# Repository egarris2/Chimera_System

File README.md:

View this project on [CADLAB.io](https://cadlab.io/project/27528). 

# Chimera_System
A modular PCB system designed for rapid iteration and extreme flexibility in application.

All PCBs are designed in KiCAD 7. They utilize components that are available from the easyEDA component library which allows for quick generation of manufacturing files for order of assembly from JLCPCB.

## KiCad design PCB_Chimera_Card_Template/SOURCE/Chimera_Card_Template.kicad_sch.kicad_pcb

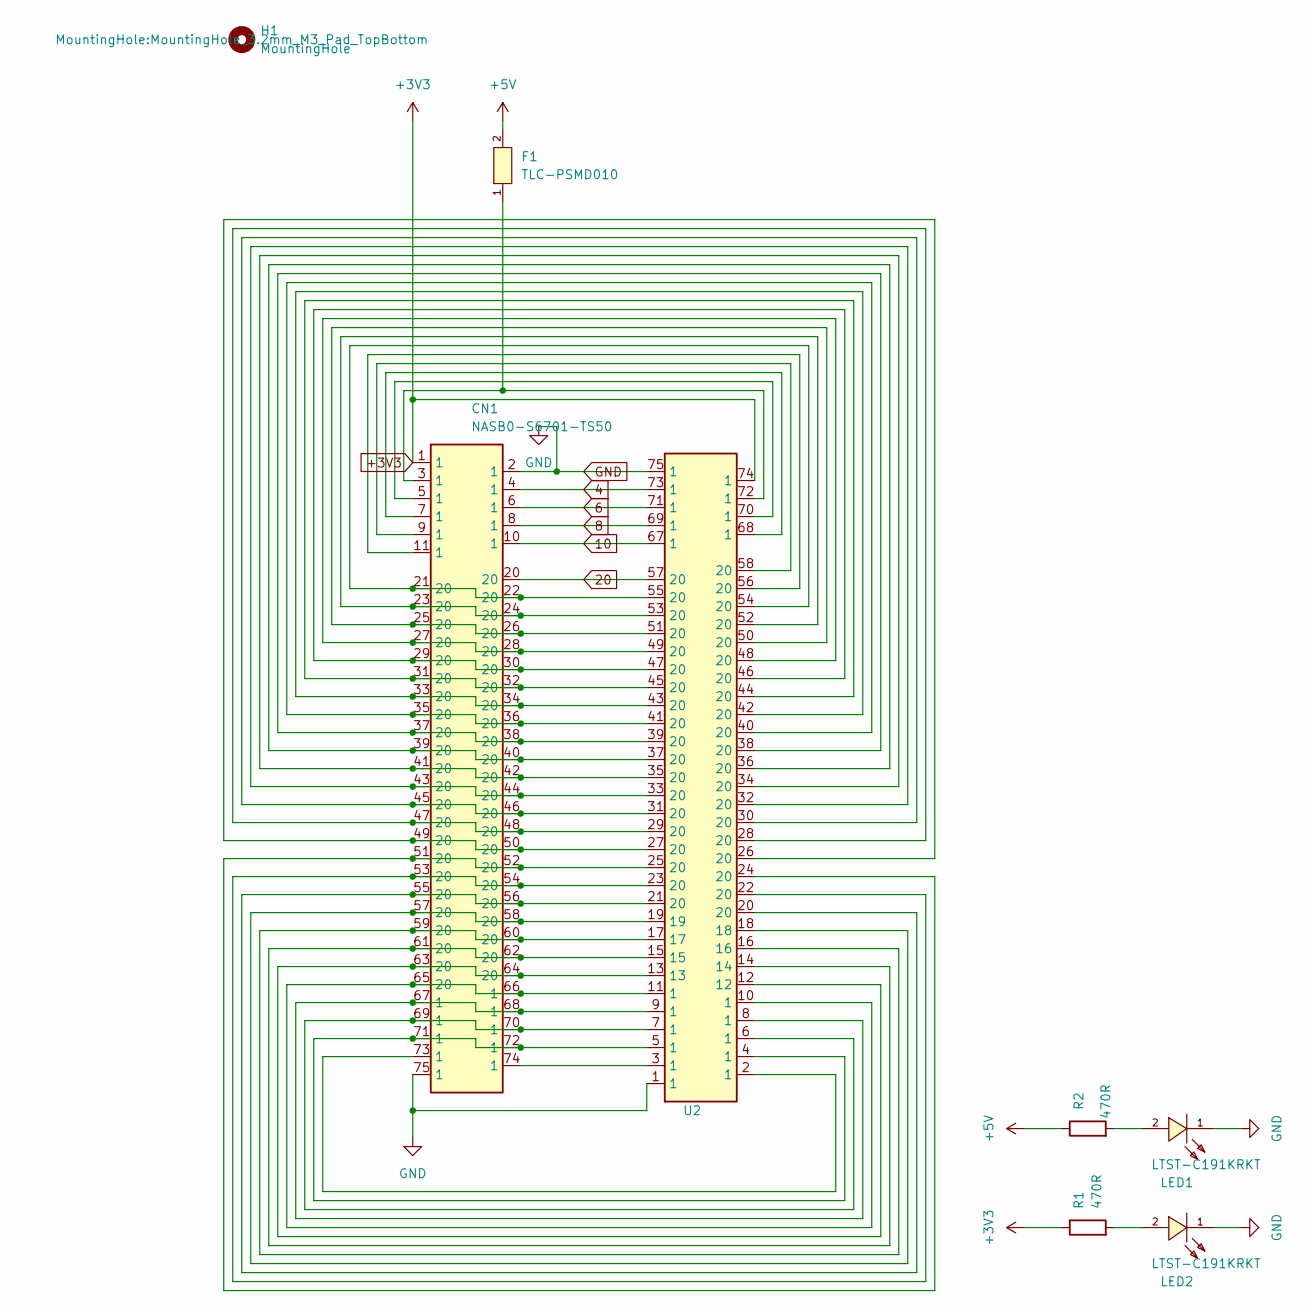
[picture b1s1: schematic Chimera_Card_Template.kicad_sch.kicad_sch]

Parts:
CN1: NASB0-S6701-TS50; CONN-SMD_67P-P0.50-V_NASB0-S6701-TS50; LCSC C367024
F1: TLC-PSMD010; F0805; LCSC C261939
H1: MountingHole; MountingHole_3.2mm_M3_Pad_TopBottom
LED1, LED2: LTST-C191KRKT; LED0603-RD; LCSC C125099
R1, R2: 470R; R_0603_1608Metric
U2: NGFF_M

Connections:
4: CN1.4 (1), U2.73 (1)
6: CN1.6 (1), U2.71 (1)
8: CN1.8 (1), U2.69 (1)
10: CN1.10 (1), U2.67 (1)
20: CN1.20, U2.57 (20)
+3V3: CN1.1, R1.1, U2.74 (1)
+5V: F1.2, R2.1
GND: CN1.2 (1), CN1.75 (1), LED1.1 (-), LED2.1 (-), U2.1, U2.75 (1)
unnamed: CN1.3 (1), F1.1, U2.72 (1)
unnamed: CN1.5 (1), U2.70 (1)
unnamed: CN1.7 (1), U2.68 (1)
unnamed: CN1.9 (1), U2.58 (20)
unnamed: CN1.11 (1), U2.56 (20)
unnamed: CN1.65 (20), CN1.66 (1), U2.10 (1), U2.11 (1)
unnamed: CN1.67 (1), CN1.68 (1), U2.8 (1), U2.9 (1)
unnamed: CN1.69 (1), CN1.70 (1), U2.6 (1), U2.7 (1)
unnamed: CN1.71 (1), CN1.72 (1), U2.4 (1), U2.5 (1)
unnamed: CN1.73 (1), U2.2 (1)
unnamed: CN1.74 (1), U2.3 (1)
unnamed: CN1.21 (20), CN1.22 (20), U2.54 (20), U2.55 (20)
unnamed: CN1.23 (20), CN1.24 (20), U2.52 (20), U2.53 (20)
unnamed: CN1.25 (20), CN1.26 (20), U2.50 (20), U2.51 (20)
unnamed: CN1.27 (20), CN1.28 (20), U2.48 (20), U2.49 (20)
unnamed: CN1.29 (20), CN1.30 (20), U2.46 (20), U2.47 (20)
unnamed: CN1.31 (20), CN1.32 (20), U2.44 (20), U2.45 (20)
unnamed: CN1.33 (20), CN1.34 (20), U2.42 (20), U2.43 (20)
unnamed: CN1.35 (20), CN1.36 (20), U2.40 (20), U2.41 (20)
unnamed: CN1.37 (20), CN1.38 (20), U2.38 (20), U2.39 (20)
unnamed: CN1.39 (20), CN1.40 (20), U2.36 (20), U2.37 (20)
unnamed: CN1.41 (20), CN1.42 (20), U2.34 (20), U2.35 (20)
unnamed: CN1.43 (20), CN1.44 (20), U2.32 (20), U2.33 (20)
unnamed: CN1.45 (20), CN1.46 (20), U2.30 (20), U2.31 (20)
unnamed: CN1.47 (20), CN1.48 (20), U2.28 (20), U2.29 (20)
unnamed: CN1.49 (20), CN1.50 (20), U2.26 (20), U2.27 (20)
unnamed: CN1.51 (20), CN1.52 (20), U2.24 (20), U2.25 (20)
unnamed: CN1.53 (20), CN1.54 (20), U2.22 (20), U2.23 (20)
unnamed: CN1.55 (20), CN1.56 (20), U2.20, U2.21 (20)
unnamed: CN1.57 (20), CN1.58 (20), U2.18, U2.19
unnamed: CN1.59 (20), CN1.60 (20), U2.16, U2.17
unnamed: CN1.61 (20), CN1.62 (20), U2.14, U2.15
unnamed: CN1.63 (20), CN1.64 (20), U2.12, U2.13
unnamed: LED1.2 (+), R2.2
unnamed: LED2.2 (+), R1.2

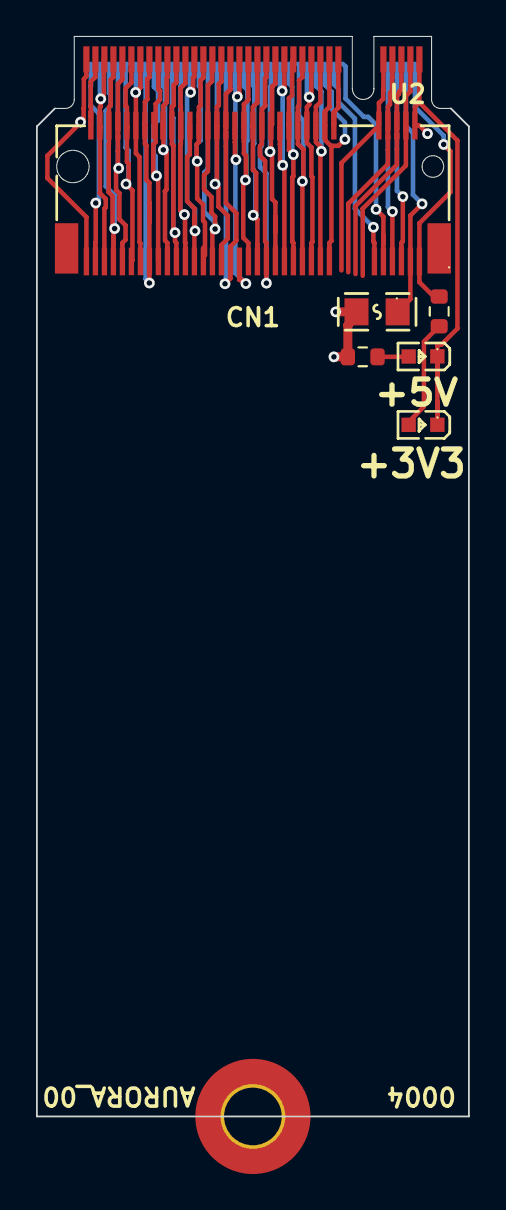
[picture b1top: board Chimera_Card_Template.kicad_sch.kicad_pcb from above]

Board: 4 copper layers, 24.0 x 60.0 mm, 8 parts (0 on the bottom side), 43 nets.

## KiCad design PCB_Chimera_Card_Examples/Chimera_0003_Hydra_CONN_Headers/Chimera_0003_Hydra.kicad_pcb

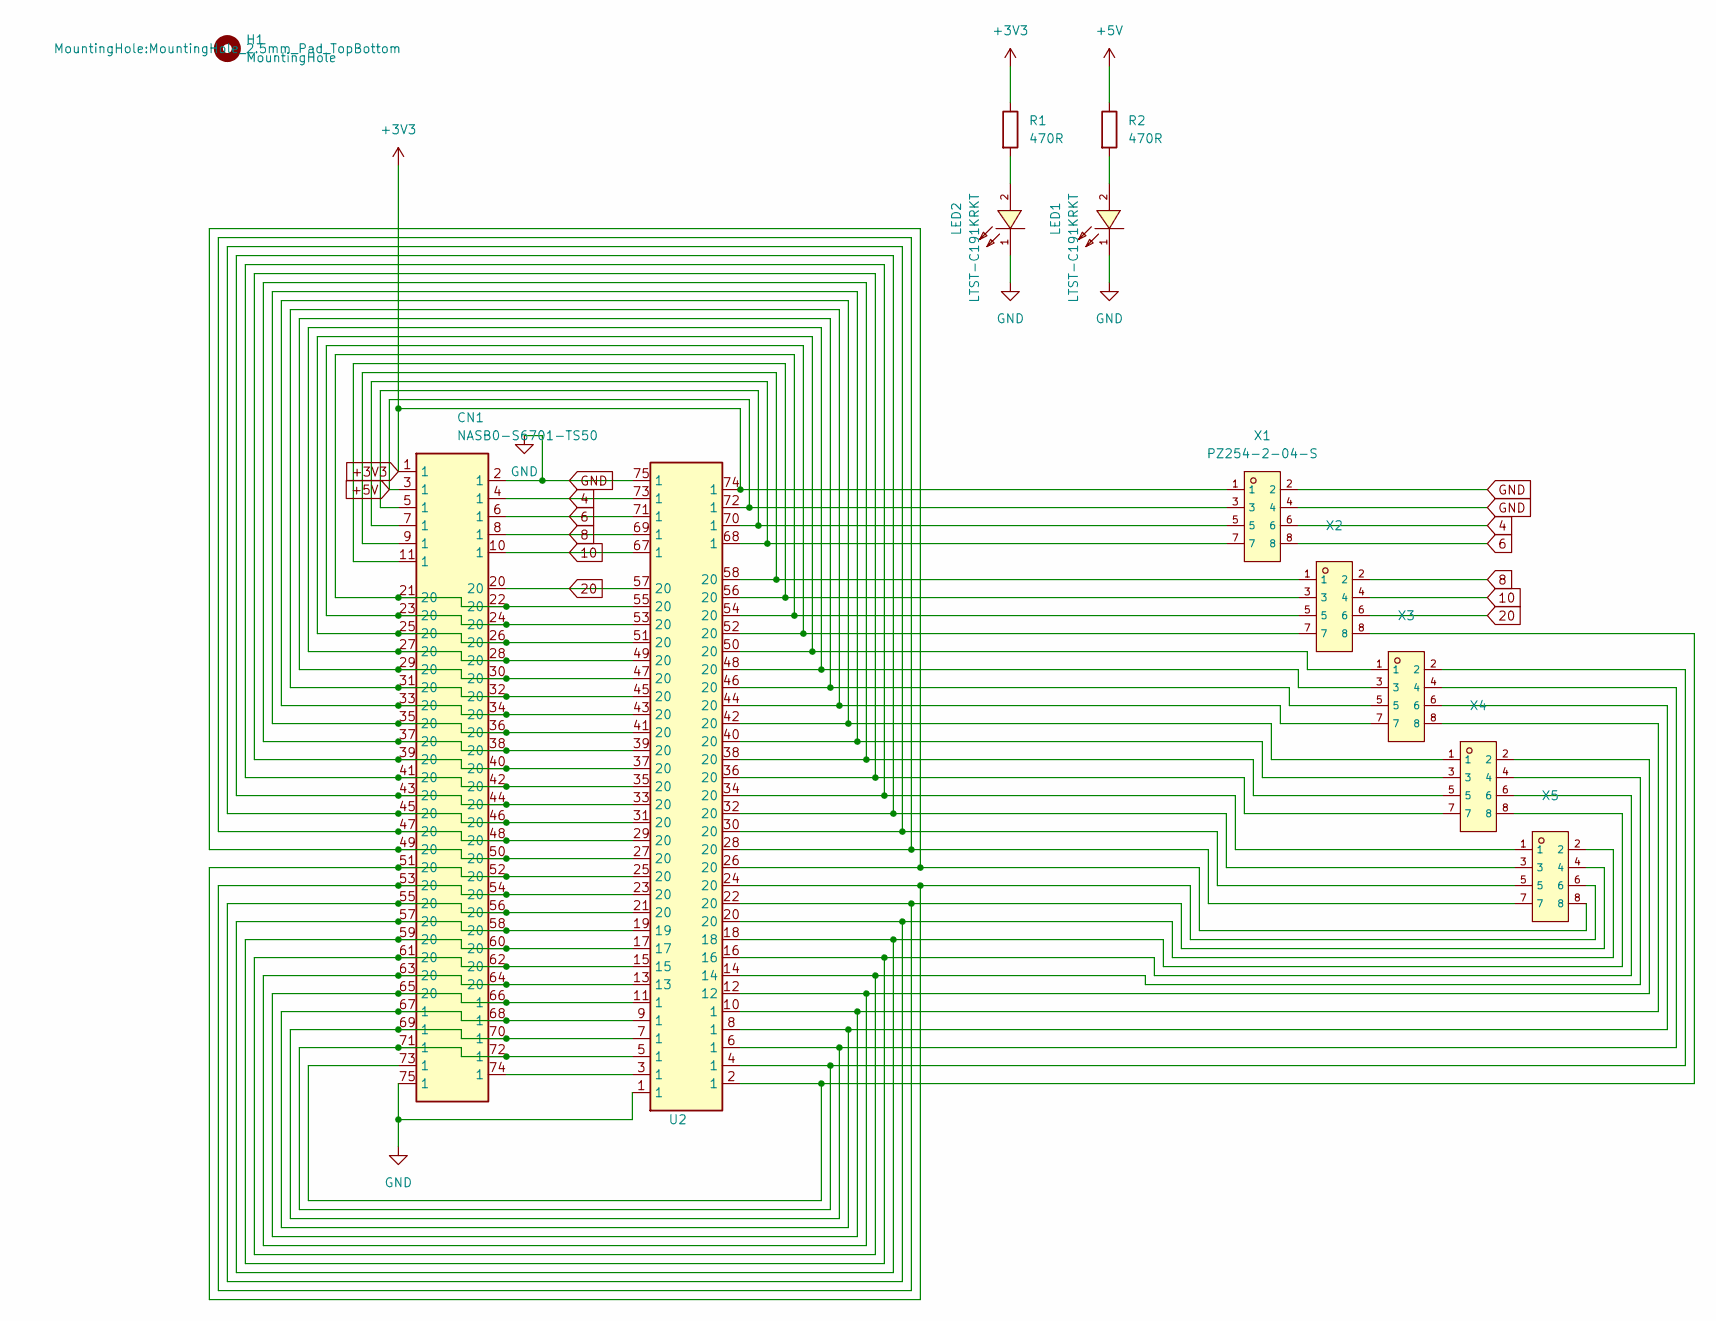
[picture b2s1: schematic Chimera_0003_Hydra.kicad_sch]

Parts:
CN1: NASB0-S6701-TS50; CONN-SMD_67P-P0.50-V_NASB0-S6701-TS50; LCSC C367024
H1: MountingHole; MountingHole_2.5mm_Pad_TopBottom
LED1, LED2: LTST-C191KRKT; LED0603-RD; LCSC C125099
R1, R2: 470R; R_0603_1608Metric
U2: NGFF_M
X1, X2, X3, X4, X5: PZ254-2-04-S; HDR-SMD_8P-P2.54-V-M-R2-C4-LS7.4; LCSC C3294462

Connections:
4: CN1.4 (1), U2.73 (1), X1.6
6: CN1.6 (1), U2.71 (1), X1.8
8: CN1.8 (1), U2.69 (1), X2.2
10: CN1.10 (1), U2.67 (1), X2.4
20: CN1.20, U2.57 (20), X2.6
+3V3: CN1.1, R1.1, U2.74 (1), X1.1
+5V: CN1.3 (1), R2.1, U2.72 (1), X1.3
GND: CN1.2 (1), CN1.75 (1), LED1.1 (-), LED2.1 (-), U2.1, U2.75 (1), X1.2, X1.4
unnamed: CN1.5 (1), U2.70 (1), X1.5
unnamed: CN1.7 (1), U2.68 (1), X1.7
unnamed: CN1.9 (1), U2.58 (20), X2.1
unnamed: CN1.11 (1), U2.56 (20), X2.3
unnamed: CN1.65 (20), CN1.66 (1), U2.10 (1), U2.11 (1), X3.8
unnamed: CN1.67 (1), CN1.68 (1), U2.8 (1), U2.9 (1), X3.6
unnamed: CN1.69 (1), CN1.70 (1), U2.6 (1), U2.7 (1), X3.4
unnamed: CN1.71 (1), CN1.72 (1), U2.4 (1), U2.5 (1), X3.2
unnamed: CN1.73 (1), U2.2 (1), X2.8
unnamed: CN1.74 (1), U2.3 (1)
unnamed: CN1.21 (20), CN1.22 (20), U2.54 (20), U2.55 (20), X2.5
unnamed: CN1.23 (20), CN1.24 (20), U2.52 (20), U2.53 (20), X2.7
unnamed: CN1.25 (20), CN1.26 (20), U2.50 (20), U2.51 (20), X3.1
unnamed: CN1.27 (20), CN1.28 (20), U2.48 (20), U2.49 (20), X3.3
unnamed: CN1.29 (20), CN1.30 (20), U2.46 (20), U2.47 (20), X3.5
unnamed: CN1.31 (20), CN1.32 (20), U2.44 (20), U2.45 (20), X3.7
unnamed: CN1.33 (20), CN1.34 (20), U2.42 (20), U2.43 (20), X4.1
unnamed: CN1.35 (20), CN1.36 (20), U2.40 (20), U2.41 (20), X4.3
unnamed: CN1.37 (20), CN1.38 (20), U2.38 (20), U2.39 (20), X4.5
unnamed: CN1.39 (20), CN1.40 (20), U2.36 (20), U2.37 (20), X4.7
unnamed: CN1.41 (20), CN1.42 (20), U2.34 (20), U2.35 (20), X5.1
unnamed: CN1.43 (20), CN1.44 (20), U2.32 (20), U2.33 (20), X5.3
unnamed: CN1.45 (20), CN1.46 (20), U2.30 (20), U2.31 (20), X5.5
unnamed: CN1.47 (20), CN1.48 (20), U2.28 (20), U2.29 (20), X5.7
unnamed: CN1.49 (20), CN1.50 (20), U2.26 (20), U2.27 (20), X5.8
unnamed: CN1.51 (20), CN1.52 (20), U2.24 (20), U2.25 (20), X5.6
unnamed: CN1.53 (20), CN1.54 (20), U2.22 (20), U2.23 (20), X5.4
unnamed: CN1.55 (20), CN1.56 (20), U2.20, U2.21 (20), X5.2
unnamed: CN1.57 (20), CN1.58 (20), U2.18, U2.19, X4.8
unnamed: CN1.59 (20), CN1.60 (20), U2.16, U2.17, X4.6
unnamed: CN1.61 (20), CN1.62 (20), U2.14, U2.15, X4.4
unnamed: CN1.63 (20), CN1.64 (20), U2.12, U2.13, X4.2
unnamed: LED1.2 (+), R2.2
unnamed: LED2.2 (+), R1.2

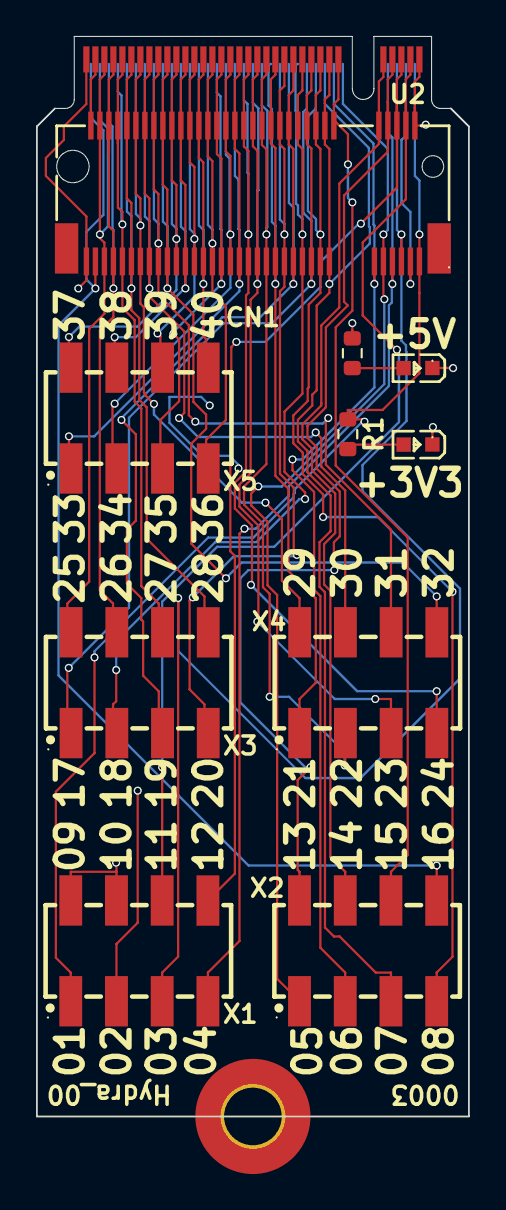
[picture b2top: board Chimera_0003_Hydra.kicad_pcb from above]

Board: 4 copper layers, 24.0 x 60.0 mm, 12 parts (0 on the bottom side), 42 nets.

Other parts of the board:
H2: MountingHole; MountingHole_3.2mm_M3_Pad_TopBottom

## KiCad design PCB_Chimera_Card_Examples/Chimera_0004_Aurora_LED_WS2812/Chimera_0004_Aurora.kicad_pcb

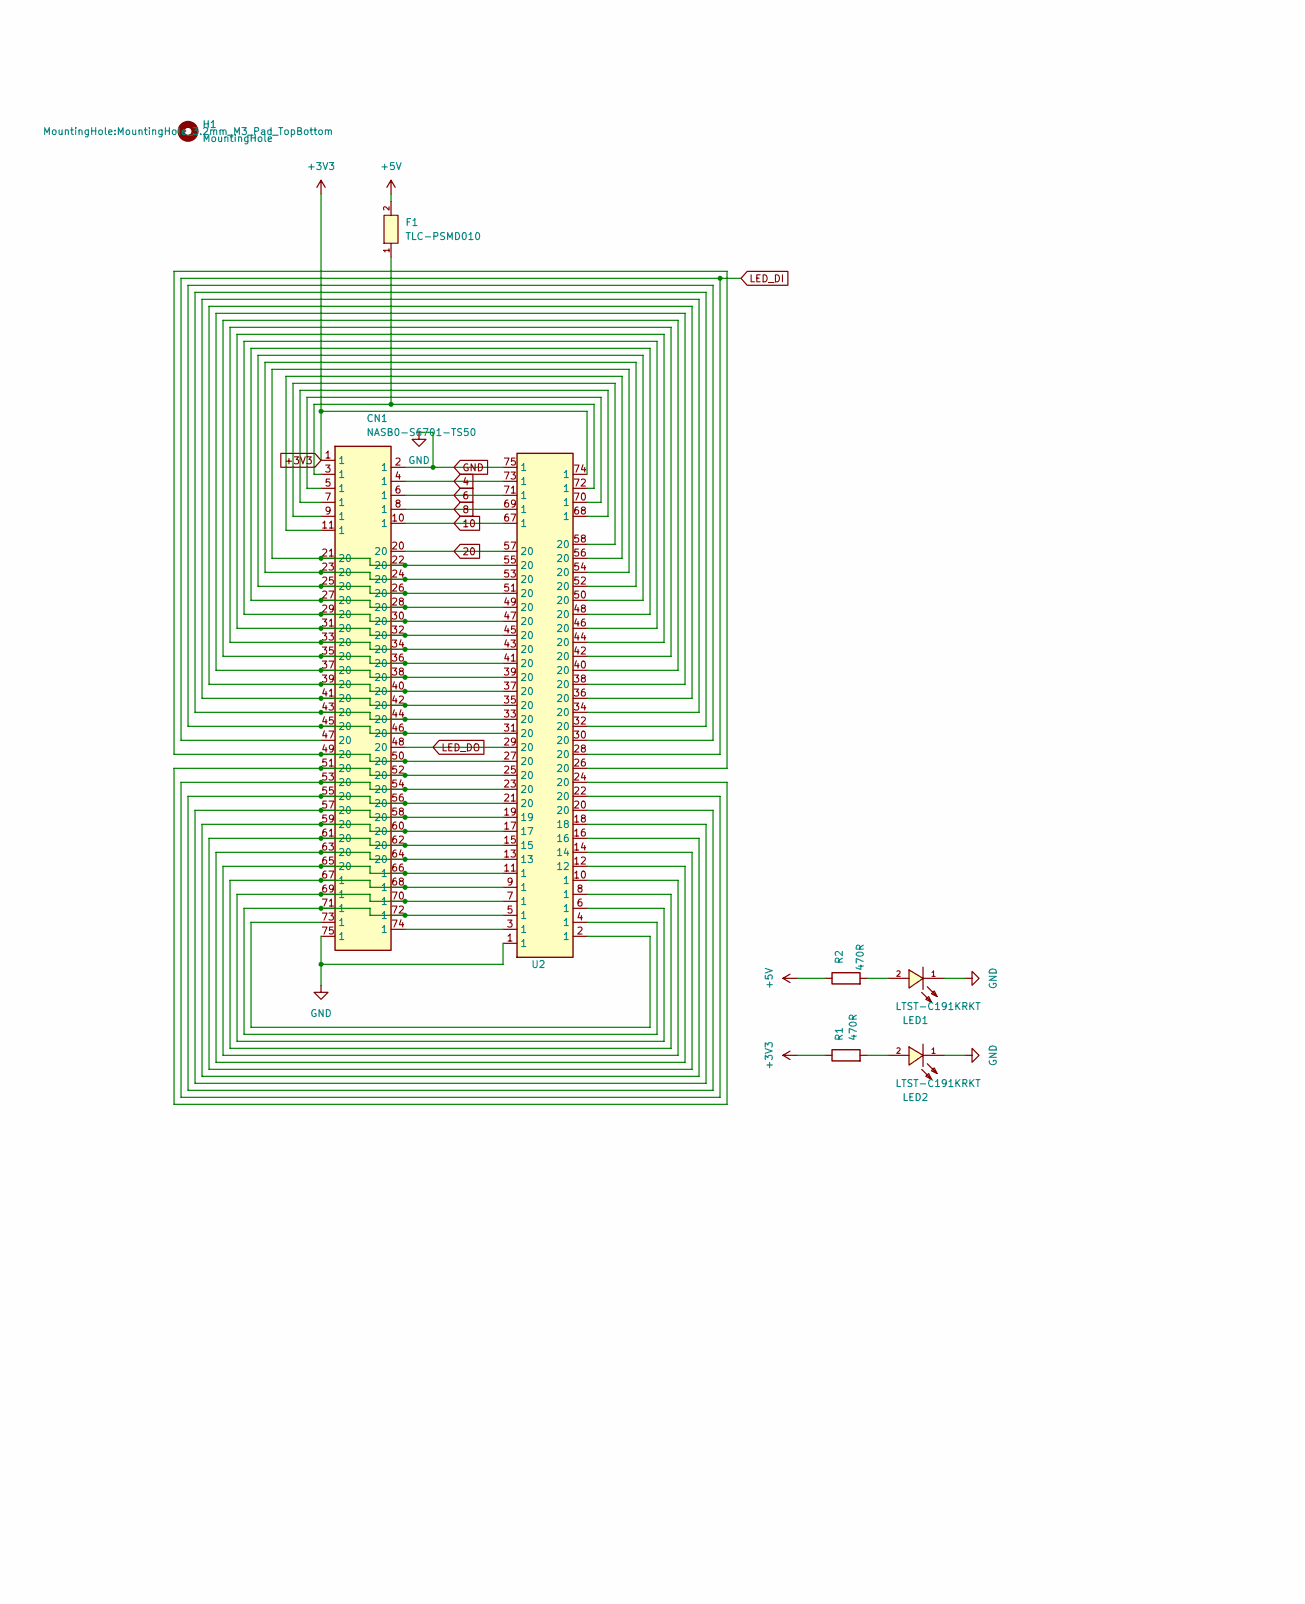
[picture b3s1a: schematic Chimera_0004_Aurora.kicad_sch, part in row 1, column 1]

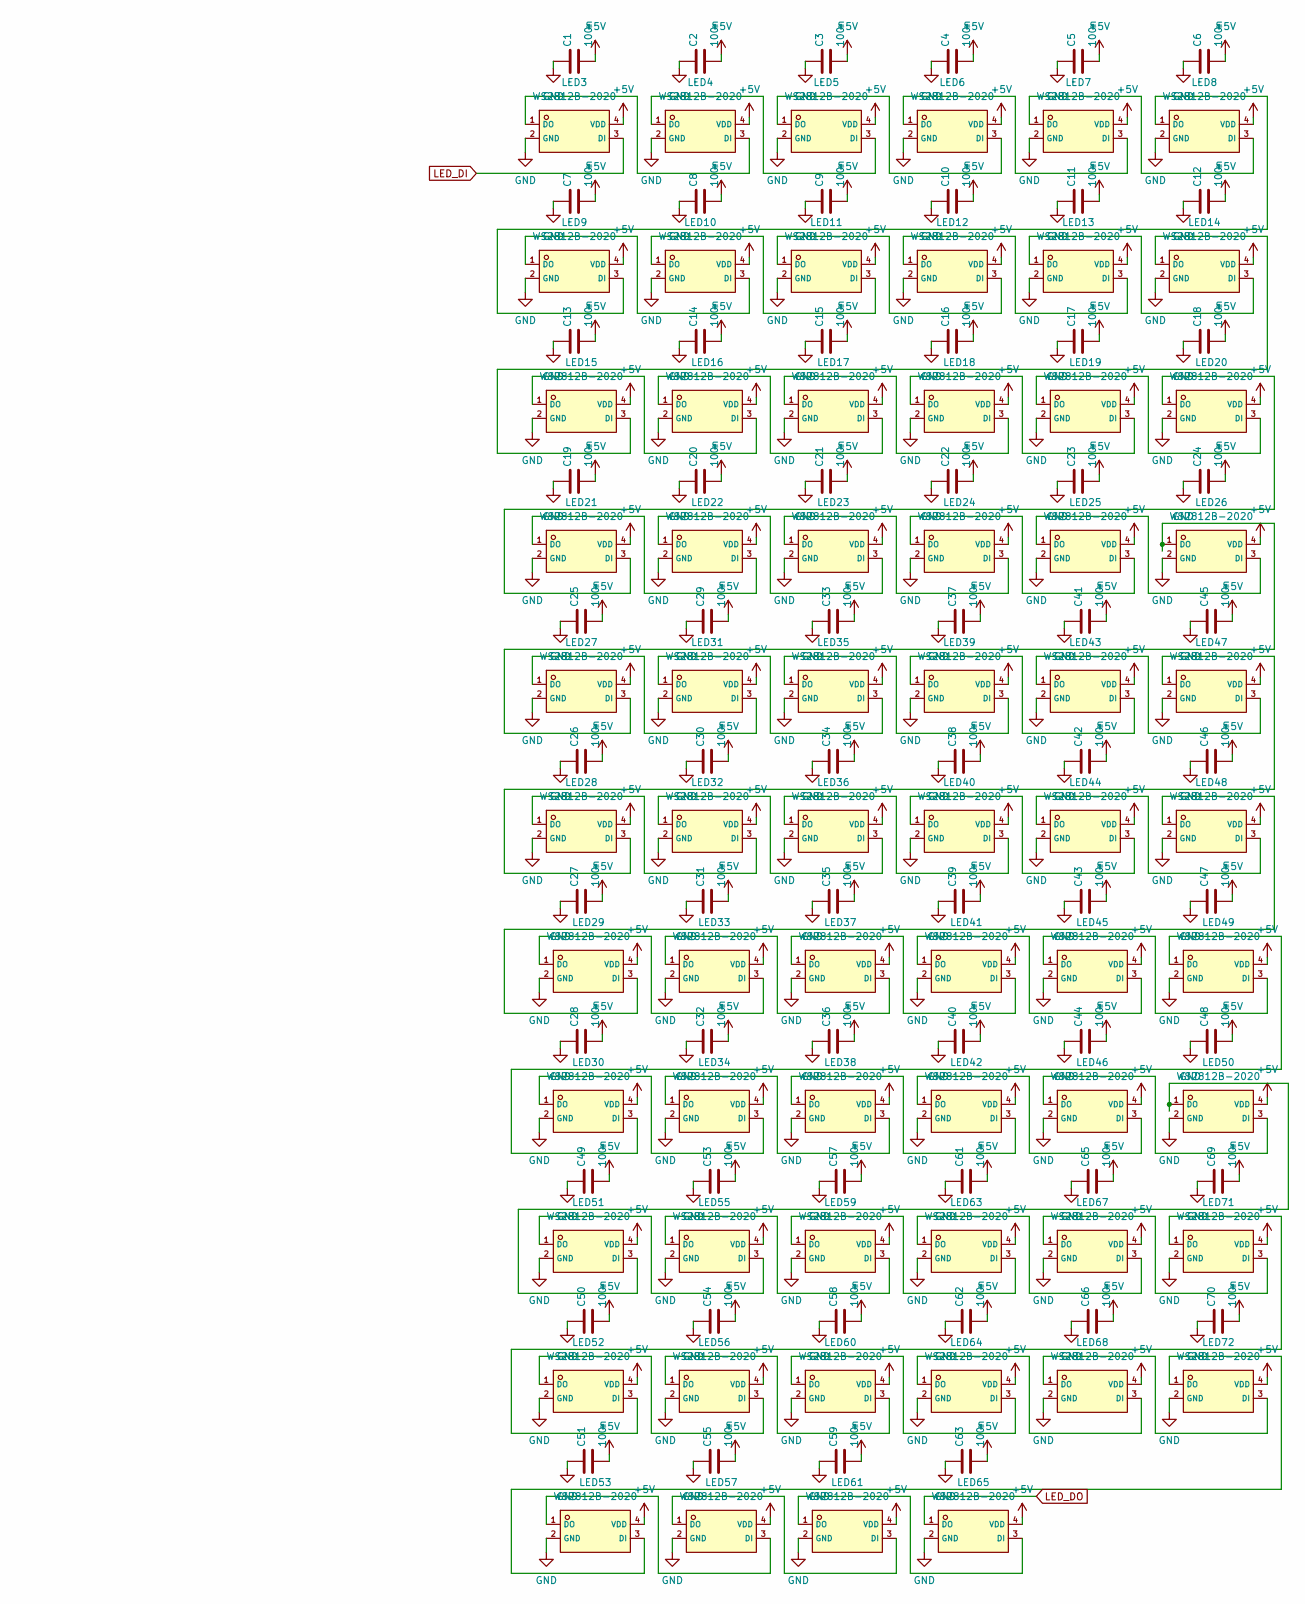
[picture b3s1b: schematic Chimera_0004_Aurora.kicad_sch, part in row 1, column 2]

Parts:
C1, C2, C3, C4, C5, C6, C7, C8, C9, C10, C11, C12, C13, C14, C15, C16, C17, C18, C19, C20, C21, C22, C23, C24, C25, C26, C27, C28, C29, C30, C31, C32, C33, C34, C35, C36, C37, C38, C39, C40, C41, C42, C43, C44, C45, C46, C47, C48, C49, C50, C51, C53, C54, C55, C57, C58, C59, C61, C62, C63, C65, C66, C69, C70: 100n; C_0402_1005Metric
CN1: NASB0-S6701-TS50; CONN-SMD_67P-P0.50-V_NASB0-S6701-TS50; LCSC C367024
F1: TLC-PSMD010; F0805; LCSC C261939
H1: MountingHole; MountingHole_3.2mm_M3_Pad_TopBottom
LED1, LED2: LTST-C191KRKT; LED0603-RD; LCSC C125099
LED3, LED4, LED5, LED6, LED7, LED8, LED9, LED10, LED11, LED12, LED13, LED14, LED15, LED16, LED17, LED18, LED19, LED20, LED21, LED22, LED23, LED24, LED25, LED26, LED27, LED28, LED29, LED30, LED31, LED32, LED33, LED34, LED35, LED36, LED37, LED38, LED39, LED40, LED41, LED42, LED43, LED44, LED45, LED46, LED47, LED48, LED49, LED50, LED51, LED52, LED53, LED55, LED56, LED57, LED59, LED60, LED61, LED63, LED64, LED65, LED67, LED68, LED71, LED72: WS2812B-2020; LED-SMD_4P-L2.0-W2.0-TL_WS2812B-2020; LCSC C965555
R1, R2: 470R; R_0603_1608Metric
U2: NGFF_M

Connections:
4: CN1.4 (1), U2.73 (1)
6: CN1.6 (1), U2.71 (1)
8: CN1.8 (1), U2.69 (1)
10: CN1.10 (1), U2.67 (1)
20: CN1.20, U2.57 (20)
+3V3: CN1.1, R1.1, U2.74 (1)
+5V: C1.2, C2.2, C3.2, C4.2, C5.2, C6.2, C7.2, C8.2, C9.2, C10.2, C11.2, C12.2, C13.2, C14.2, C15.2, C16.2, C17.2, C18.2, C19.2, C20.2, C21.2, C22.2, C23.2, C24.2, C25.2, C26.2, C27.2, C28.2, C29.2, C30.2, C31.2, C32.2, C33.2, C34.2, C35.2, C36.2, C37.2, C38.2, C39.2, C40.2, C41.2, C42.2, C43.2, C44.2, C45.2, C46.2, C47.2, C48.2, C49.2, C50.2, C51.2, C53.2, C54.2, C55.2, C57.2, C58.2, C59.2, C61.2, C62.2, C63.2, C65.2, C66.2, C69.2, C70.2, F1.2, LED3.4 (VDD), LED4.4 (VDD), LED5.4 (VDD), LED6.4 (VDD), LED7.4 (VDD), LED8.4 (VDD), LED9.4 (VDD), LED10.4 (VDD), LED11.4 (VDD), LED12.4 (VDD), LED13.4 (VDD), LED14.4 (VDD), LED15.4 (VDD), LED16.4 (VDD), LED17.4 (VDD), LED18.4 (VDD), LED19.4 (VDD), LED20.4 (VDD), LED21.4 (VDD), LED22.4 (VDD), LED23.4 (VDD), LED24.4 (VDD), LED25.4 (VDD), LED26.4 (VDD), LED27.4 (VDD), LED28.4 (VDD), LED29.4 (VDD), LED30.4 (VDD), LED31.4 (VDD), LED32.4 (VDD), LED33.4 (VDD), LED34.4 (VDD), LED35.4 (VDD), LED36.4 (VDD), LED37.4 (VDD), LED38.4 (VDD), LED39.4 (VDD), LED40.4 (VDD), LED41.4 (VDD), LED42.4 (VDD), LED43.4 (VDD), LED44.4 (VDD), LED45.4 (VDD), LED46.4 (VDD), LED47.4 (VDD), LED48.4 (VDD), LED49.4 (VDD), LED50.4 (VDD), LED51.4 (VDD), LED52.4 (VDD), LED53.4 (VDD), LED55.4 (VDD), LED56.4 (VDD), LED57.4 (VDD), LED59.4 (VDD), LED60.4 (VDD), LED61.4 (VDD), LED63.4 (VDD), LED64.4 (VDD), LED65.4 (VDD), LED67.4 (VDD), LED68.4 (VDD), LED71.4 (VDD), LED72.4 (VDD), R2.1
GND: C1.1, C2.1, C3.1, C4.1, C5.1, C6.1, C7.1, C8.1, C9.1, C10.1, C11.1, C12.1, C13.1, C14.1, C15.1, C16.1, C17.1, C18.1, C19.1, C20.1, C21.1, C22.1, C23.1, C24.1, C25.1, C26.1, C27.1, C28.1, C29.1, C30.1, C31.1, C32.1, C33.1, C34.1, C35.1, C36.1, C37.1, C38.1, C39.1, C40.1, C41.1, C42.1, C43.1, C44.1, C45.1, C46.1, C47.1, C48.1, C49.1, C50.1, C51.1, C53.1, C54.1, C55.1, C57.1, C58.1, C59.1, C61.1, C62.1, C63.1, C65.1, C66.1, C69.1, C70.1, CN1.2 (1), CN1.75 (1), LED1.1 (-), LED2.1 (-), LED3.2 (GND), LED4.2 (GND), LED5.2 (GND), LED6.2 (GND), LED7.2 (GND), LED8.2 (GND), LED9.2 (GND), LED10.2 (GND), LED11.2 (GND), LED12.2 (GND), LED13.2 (GND), LED14.2 (GND), LED15.2 (GND), LED16.2 (GND), LED17.2 (GND), LED18.2 (GND), LED19.2 (GND), LED20.2 (GND), LED21.2 (GND), LED22.2 (GND), LED23.2 (GND), LED24.2 (GND), LED25.2 (GND), LED26.2 (GND), LED27.2 (GND), LED28.2 (GND), LED29.2 (GND), LED30.2 (GND), LED31.2 (GND), LED32.2 (GND), LED33.2 (GND), LED34.2 (GND), LED35.2 (GND), LED36.2 (GND), LED37.2 (GND), LED38.2 (GND), LED39.2 (GND), LED40.2 (GND), LED41.2 (GND), LED42.2 (GND), LED43.2 (GND), LED44.2 (GND), LED45.2 (GND), LED46.2 (GND), LED47.2 (GND), LED48.2 (GND), LED49.2 (GND), LED50.2 (GND), LED51.2 (GND), LED52.2 (GND), LED53.2 (GND), LED55.2 (GND), LED56.2 (GND), LED57.2 (GND), LED59.2 (GND), LED60.2 (GND), LED61.2 (GND), LED63.2 (GND), LED64.2 (GND), LED65.2 (GND), LED67.2 (GND), LED68.2 (GND), LED71.2 (GND), LED72.2 (GND), U2.1, U2.75 (1)
LED_DI: CN1.47 (20), LED3.3 (DI), U2.28 (20)
LED_DO: CN1.48 (20), LED65.1 (DO), U2.29 (20)
unnamed: CN1.3 (1), F1.1, U2.72 (1)
unnamed: CN1.5 (1), U2.70 (1)
unnamed: CN1.7 (1), U2.68 (1)
unnamed: CN1.9 (1), U2.58 (20)
unnamed: CN1.11 (1), U2.56 (20)
unnamed: CN1.65 (20), CN1.66 (1), U2.10 (1), U2.11 (1)
unnamed: CN1.67 (1), CN1.68 (1), U2.8 (1), U2.9 (1)
unnamed: CN1.69 (1), CN1.70 (1), U2.6 (1), U2.7 (1)
unnamed: CN1.71 (1), CN1.72 (1), U2.4 (1), U2.5 (1)
unnamed: CN1.73 (1), U2.2 (1)
unnamed: CN1.74 (1), U2.3 (1)
unnamed: CN1.21 (20), CN1.22 (20), U2.54 (20), U2.55 (20)
unnamed: CN1.23 (20), CN1.24 (20), U2.52 (20), U2.53 (20)
unnamed: CN1.25 (20), CN1.26 (20), U2.50 (20), U2.51 (20)
unnamed: CN1.27 (20), CN1.28 (20), U2.48 (20), U2.49 (20)
unnamed: CN1.29 (20), CN1.30 (20), U2.46 (20), U2.47 (20)
unnamed: CN1.31 (20), CN1.32 (20), U2.44 (20), U2.45 (20)
unnamed: CN1.33 (20), CN1.34 (20), U2.42 (20), U2.43 (20)
unnamed: CN1.35 (20), CN1.36 (20), U2.40 (20), U2.41 (20)
unnamed: CN1.37 (20), CN1.38 (20), U2.38 (20), U2.39 (20)
unnamed: CN1.39 (20), CN1.40 (20), U2.36 (20), U2.37 (20)
unnamed: CN1.41 (20), CN1.42 (20), U2.34 (20), U2.35 (20)
unnamed: CN1.43 (20), CN1.44 (20), U2.32 (20), U2.33 (20)
unnamed: CN1.45 (20), CN1.46 (20), U2.30 (20), U2.31 (20)
unnamed: CN1.49 (20), CN1.50 (20), U2.26 (20), U2.27 (20)
unnamed: CN1.51 (20), CN1.52 (20), U2.24 (20), U2.25 (20)
unnamed: CN1.53 (20), CN1.54 (20), U2.22 (20), U2.23 (20)
unnamed: CN1.55 (20), CN1.56 (20), U2.20, U2.21 (20)
unnamed: CN1.57 (20), CN1.58 (20), U2.18, U2.19
unnamed: CN1.59 (20), CN1.60 (20), U2.16, U2.17
unnamed: CN1.61 (20), CN1.62 (20), U2.14, U2.15
unnamed: CN1.63 (20), CN1.64 (20), U2.12, U2.13
unnamed: LED1.2 (+), R2.2
unnamed: LED2.2 (+), R1.2
unnamed: LED3.1 (DO), LED4.3 (DI)
unnamed: LED4.1 (DO), LED5.3 (DI)
unnamed: LED5.1 (DO), LED6.3 (DI)
unnamed: LED6.1 (DO), LED7.3 (DI)
unnamed: LED7.1 (DO), LED8.3 (DI)
unnamed: LED8.1 (DO), LED9.3 (DI)
unnamed: LED9.1 (DO), LED10.3 (DI)
unnamed: LED10.1 (DO), LED11.3 (DI)
unnamed: LED11.1 (DO), LED12.3 (DI)
unnamed: LED12.1 (DO), LED13.3 (DI)
unnamed: LED13.1 (DO), LED14.3 (DI)
unnamed: LED14.1 (DO), LED15.3 (DI)
unnamed: LED15.1 (DO), LED16.3 (DI)
unnamed: LED16.1 (DO), LED17.3 (DI)
unnamed: LED17.1 (DO), LED18.3 (DI)
unnamed: LED18.1 (DO), LED19.3 (DI)
unnamed: LED19.1 (DO), LED20.3 (DI)
unnamed: LED20.1 (DO), LED21.3 (DI)
unnamed: LED21.1 (DO), LED22.3 (DI)
unnamed: LED22.1 (DO), LED23.3 (DI)
unnamed: LED23.1 (DO), LED24.3 (DI)
unnamed: LED24.1 (DO), LED25.3 (DI)
unnamed: LED25.1 (DO), LED26.3 (DI)
unnamed: LED26.1 (DO), LED27.3 (DI)
unnamed: LED27.1 (DO), LED31.3 (DI)
unnamed: LED28.3 (DI), LED47.1 (DO)
unnamed: LED28.1 (DO), LED32.3 (DI)
unnamed: LED29.3 (DI), LED48.1 (DO)
unnamed: LED29.1 (DO), LED33.3 (DI)
unnamed: LED30.3 (DI), LED49.1 (DO)
unnamed: LED30.1 (DO), LED34.3 (DI)
unnamed: LED31.1 (DO), LED35.3 (DI)
unnamed: LED32.1 (DO), LED36.3 (DI)
unnamed: LED33.1 (DO), LED37.3 (DI)
unnamed: LED34.1 (DO), LED38.3 (DI)
unnamed: LED35.1 (DO), LED39.3 (DI)
unnamed: LED36.1 (DO), LED40.3 (DI)
unnamed: LED37.1 (DO), LED41.3 (DI)
unnamed: LED38.1 (DO), LED42.3 (DI)
unnamed: LED39.1 (DO), LED43.3 (DI)
unnamed: LED40.1 (DO), LED44.3 (DI)
unnamed: LED41.1 (DO), LED45.3 (DI)
unnamed: LED42.1 (DO), LED46.3 (DI)
unnamed: LED43.1 (DO), LED47.3 (DI)
unnamed: LED44.1 (DO), LED48.3 (DI)
unnamed: LED45.1 (DO), LED49.3 (DI)
unnamed: LED46.1 (DO), LED50.3 (DI)
unnamed: LED50.1 (DO), LED51.3 (DI)
unnamed: LED51.1 (DO), LED55.3 (DI)
unnamed: LED52.3 (DI), LED71.1 (DO)
unnamed: LED52.1 (DO), LED56.3 (DI)
unnamed: LED53.3 (DI), LED72.1 (DO)
unnamed: LED53.1 (DO), LED57.3 (DI)
unnamed: LED55.1 (DO), LED59.3 (DI)
unnamed: LED56.1 (DO), LED60.3 (DI)
unnamed: LED57.1 (DO), LED61.3 (DI)
unnamed: LED59.1 (DO), LED63.3 (DI)
unnamed: LED60.1 (DO), LED64.3 (DI)
unnamed: LED61.1 (DO), LED65.3 (DI)
unnamed: LED63.1 (DO), LED67.3 (DI)
unnamed: LED64.1 (DO), LED68.3 (DI)
unnamed: LED67.1 (DO), LED71.3 (DI)
unnamed: LED68.1 (DO), LED72.3 (DI)

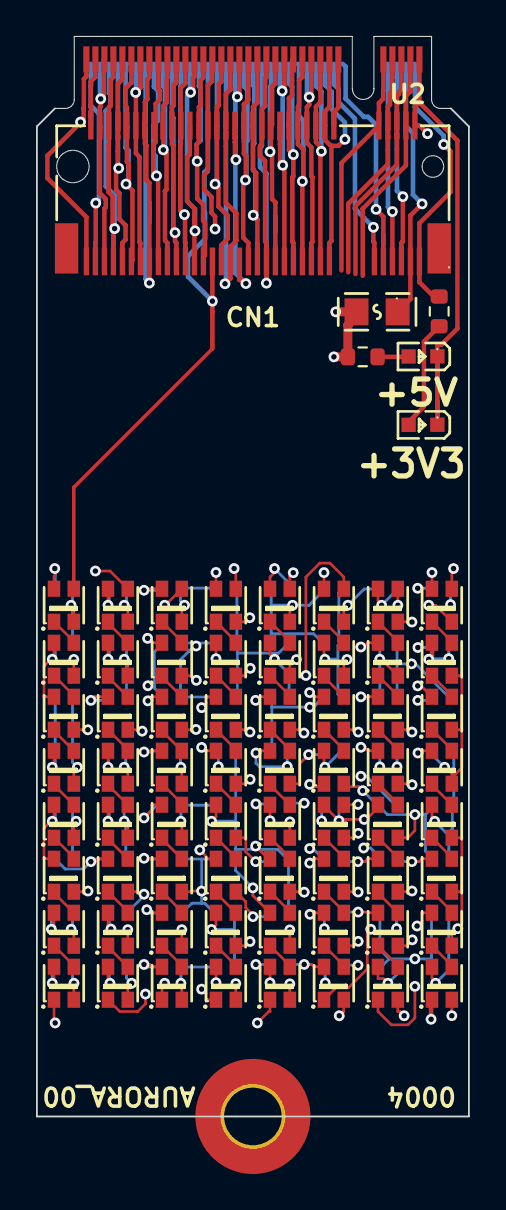
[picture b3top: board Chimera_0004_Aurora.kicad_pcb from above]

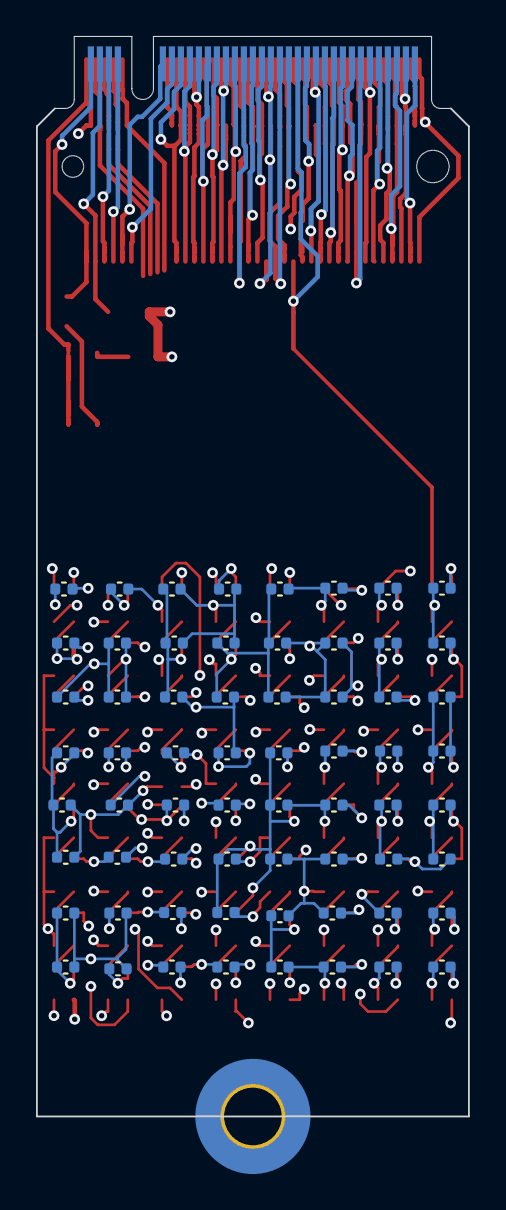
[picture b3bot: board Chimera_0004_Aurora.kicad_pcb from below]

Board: 4 copper layers, 24.0 x 60.0 mm, 136 parts (64 on the bottom side), 107 nets.

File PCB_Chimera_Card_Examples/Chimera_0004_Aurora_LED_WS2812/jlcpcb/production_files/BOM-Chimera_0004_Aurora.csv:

Comment,Designator,Footprint,LCSC
LTST-C191KRKT,"LED1,LED2",LED0603-RD,C125099
TLC-PSMD010,F1,F0805,C261939
NASB0-S6701-TS50,CN1,CONN-SMD_67P-P0.50-V_NASB0-S6701-TS50,C367024
WS2812B-2020,"LED10,LED11,LED12,LED13,LED14,LED15,LED16,LED17,LED18,LED19,LED20,LED21,LED22,LED23,LED24,LED25,LED26,LED27,LED28,LED29,LED3,LED30,LED31,LED32,LED33,LED34,LED35,LED36,LED37,LED38,LED39,LED4,LED40,LED41,LED42,LED43,LED44,LED45,LED46,LED47,LED48,LED49,LED5,LED50,LED51,LED52,LED53,LED55,LED56,LED57,LED59,LED6,LED60,LED61,LED63,LED64,LED65,LED67,LED68,LED7,LED71,LED72,LED8,LED9",LED-SMD_4P-L2.0-W2.0-TL_WS2812B-2020,C965555
MountingHole,H1,MountingHole_3.2mm_M3_Pad_TopBottom,
100n,C70,C_0402_1005Metric,
100n,C69,C_0402_1005Metric,
100n,C66,C_0402_1005Metric,
100n,C65,C_0402_1005Metric,
100n,C63,C_0402_1005Metric,
100n,C62,C_0402_1005Metric,
100n,C61,C_0402_1005Metric,
100n,C59,C_0402_1005Metric,
100n,C58,C_0402_1005Metric,
100n,C57,C_0402_1005Metric,
100n,C55,C_0402_1005Metric,
100n,C54,C_0402_1005Metric,
100n,C53,C_0402_1005Metric,
100n,C51,C_0402_1005Metric,
100n,C50,C_0402_1005Metric,
100n,C49,C_0402_1005Metric,
100n,C48,C_0402_1005Metric,
100n,C47,C_0402_1005Metric,
100n,C46,C_0402_1005Metric,
100n,C45,C_0402_1005Metric,
100n,C44,C_0402_1005Metric,
100n,C43,C_0402_1005Metric,
100n,C42,C_0402_1005Metric,
100n,C41,C_0402_1005Metric,
100n,C40,C_0402_1005Metric,
100n,C39,C_0402_1005Metric,
100n,C38,C_0402_1005Metric,
100n,C37,C_0402_1005Metric,
100n,C36,C_0402_1005Metric,
100n,C35,C_0402_1005Metric,
100n,C34,C_0402_1005Metric,
100n,C33,C_0402_1005Metric,
100n,C32,C_0402_1005Metric,
100n,C31,C_0402_1005Metric,
100n,C30,C_0402_1005Metric,
100n,C29,C_0402_1005Metric,
100n,C28,C_0402_1005Metric,
100n,C27,C_0402_1005Metric,
100n,C26,C_0402_1005Metric,
100n,C25,C_0402_1005Metric,
100n,C7,C_0402_1005Metric,
100n,C2,C_0402_1005Metric,
100n,C4,C_0402_1005Metric,
100n,C5,C_0402_1005Metric,
100n,C6,C_0402_1005Metric,
100n,C22,C_0402_1005Metric,
100n,C10,C_0402_1005Metric,
100n,C20,C_0402_1005Metric,
100n,C1,C_0402_1005Metric,
100n,C3,C_0402_1005Metric,
100n,C9,C_0402_1005Metric,
100n,C11,C_0402_1005Metric,
100n,C12,C_0402_1005Metric,
100n,C13,C_0402_1005Metric,
100n,C14,C_0402_1005Metric,
100n,C15,C_0402_1005Metric,
100n,C17,C_0402_1005Metric,
100n,C19,C_0402_1005Metric,
100n,C18,C_0402_1005Metric,
100n,C16,C_0402_1005Metric,
100n,C21,C_0402_1005Metric,
100n,C23,C_0402_1005Metric,
100n,C8,C_0402_1005Metric,
100n,C24,C_0402_1005Metric,
~,U2,NGFF_M,
470R,R1,R_0603_1608Metric,
470R,R2,R_0603_1608Metric,
